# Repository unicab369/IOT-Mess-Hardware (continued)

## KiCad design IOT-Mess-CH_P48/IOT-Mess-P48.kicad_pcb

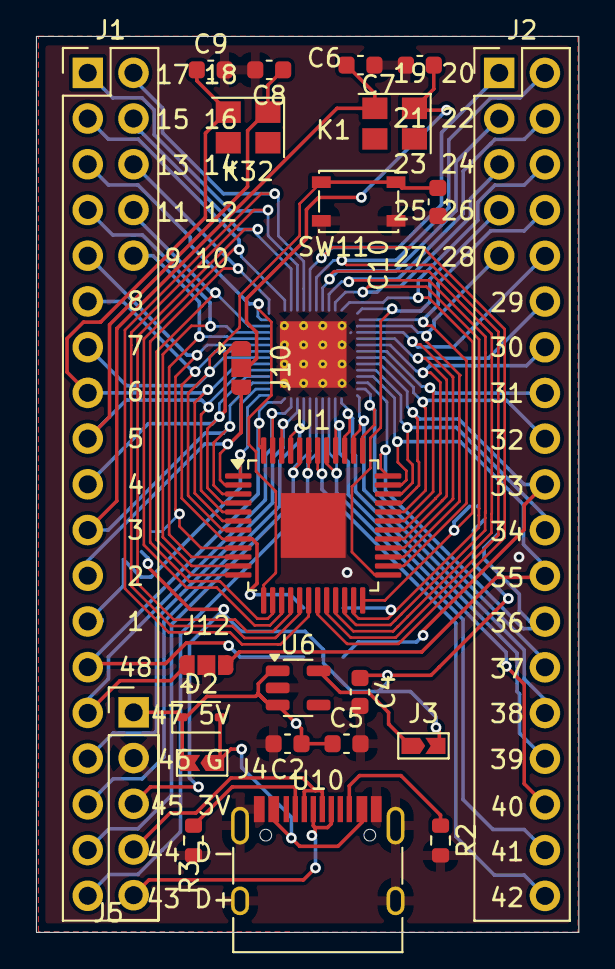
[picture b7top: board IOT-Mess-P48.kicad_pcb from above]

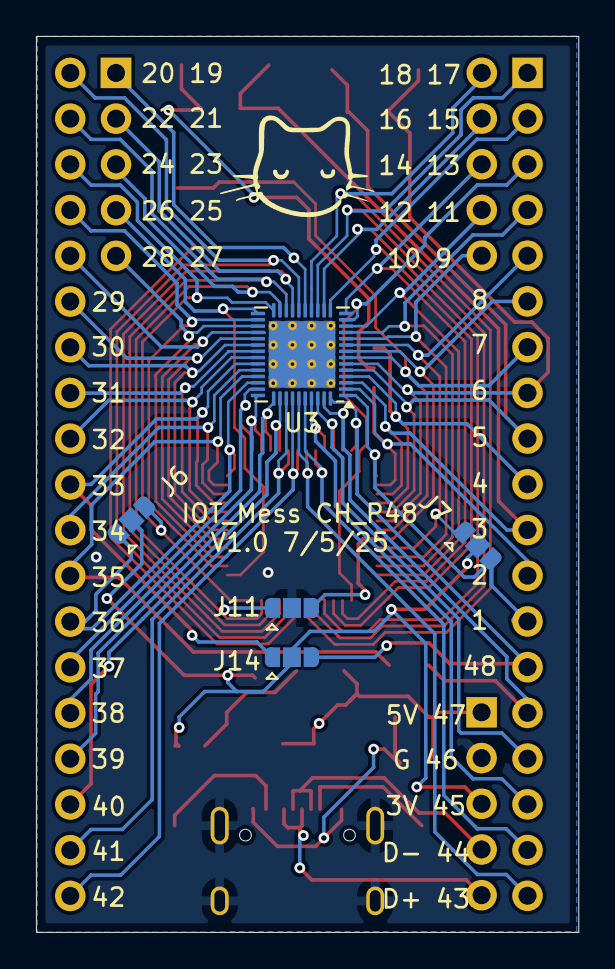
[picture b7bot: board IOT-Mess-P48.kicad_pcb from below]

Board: 2 copper layers, 30.1 x 49.8 mm, 29 parts (5 on the bottom side), 58 nets.

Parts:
C2: 10u; C_0603_1608Metric
C4, C5: 1u; C_0603_1608Metric
C6, C7: 12-25pF; C_0603_1608Metric
C8, C9: 15-30pF; C_0603_1608Metric
C10: .1u; C_0603_1608Metric
D2: 1N5819WS; D_SOD-323
J1, J2: Conn_02x19_Odd_Even; PinHeader_2x19_P2.54mm_Vertical
J3, J4: Jumper_2; Jumpper-triangle
J5: Conn_01x05_Pin; PinHeader_1x05_P2.54mm_Vertical
J6, J7, J10, J11, J12, J14: Jumper; Jumper-3_P1.3mm_Open_RoundedPad1.0x1.5mm
K1, K32: Crystal; Crystal_SMD_3225-4Pin_3.2x2.5mm
R2, R3: 5.1K; R_0603_1608Metric
SW11: SW_Push; SW_SPST_PTS810
U1: LQFP-48-1EP_7x7mm_P0.5mm_EP3.6x3.6mm
U3: CH32L103C8T6; QFN-48-1EP_5x5mm_P0.35mm_EP3.7x3.7mm_ThermalVias
U6: ME6211C33M5; SOT-23-5
U10: USB_C_Receptacle_USB2.0_16P; USB_C_Receptacle_HRO_TYPE-C-31-M-12

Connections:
5V: C2.1, C5.1, D2.1 (K), J4.2 (B), J5.1, U6.1 (V_{IN}), U6.3 (CE)
+3.3V: C4.1, J3.2 (B), J5.3, J6.2 (C), J7.2 (C), J14.2 (C)
D+: J5.5, U10.A6 (D+), U10.B6 (D+)
D-: J5.4, U10.A7 (D-), U10.B7 (D-)
GND: C2.2, C4.2, C5.2, C6.2, C7.2, C8.2, C9.2, C10.2, J5.2, J11.2 (C), J12.2 (C), R2.2, R3.2, SW11.2, U1.49 (VSS), U3.49 (VSS), U6.2 (V_{SS}), U10.A1 (GND), U10.A12 (GND), U10.B1 (GND), U10.B12 (GND), U10.S1 (SHIELD)
unnamed: D2.2 (A), J4.1 (A), U10.A4 (VBUS), U10.A9 (VBUS), U10.B4 (VBUS), U10.B9 (VBUS)
unnamed: J3.1 (A), U6.5 (V_{OUT})
unnamed: C7.1, J10.2 (C), K1.1
unnamed: R3.1, U10.A5 (CC1)
unnamed: R2.1, U10.B5 (CC2)
P_1: J1.25, J7.3 (B), U1.1 (VBAT), U3.1 (VBAT)
P_2: J1.23, J10.3 (B), U1.2 (PC13), U3.2 (PC13)
P_3: C6.1, J1.21, K1.2, U1.3 (PC14/OSC32_IN), U3.3 (PC14/OSC32_IN)
P_4: J1.19, J10.1 (A), U1.4 (PC15/OSC32_OUT), U3.4 (PC15/OSC32_OUT)
P_5: C8.1, J1.17, K32.1, U1.5 (PD0/OSC_IN), U3.5 (PD0/OSC_IN)
P_6: C9.1, J1.15, K32.2, U1.6 (PD1/OSC_OUT), U3.6 (PD1/OSC_OUT)
P_7: C10.1, J1.13, SW11.1, U1.7 (NRST), U3.7 (NRST)
P_8: J1.11, J11.3 (B), U1.8 (VSSA), U3.8 (VSSA)
P_9: J1.9, J7.1 (A), U1.9 (VDDA), U3.9 (VDDA)
P_10: J1.10, U1.10 (PA0/ADC0/WKUP), U3.10 (PA0/ADC0/WKUP)
P_11: J1.7, U1.11 (PA1/ADC1), U3.11 (PA1/ADC1)
P_12: J1.8, U1.12 (PA2/ADC2), U3.12 (PA2/ADC2)
P_13: J1.5, U1.13 (PA3/ADC3), U3.13 (PA3/ADC3)
P_14: J1.6, U1.14 (PA4/ADC), U3.14 (PA4/ADC4/ADC0)
P_15: J1.3, U1.15 (PA5/ADC5/SCK*), U3.15 (PA5/ADC5/ADC1/SCK*)
P_16: J1.4, U1.16 (PA6/ADC6/MISO*), U3.16 (PA6/ADC6/MISO*)
P_17: J1.1, U1.17 (PA7/ADC7/MOSI*), U3.17 (PA7/ADC7/MOSI*)
P_18: J1.2, U1.18 (PB0/ADC8), U3.18 (PB0/ADC8)
P_19: J2.1, U1.19 (PB1/ADC9), U3.19 (PB1/ADC9)
P_20: J2.2, U1.20 (PB2/BOTT), U3.20 (PB2/BOOT)
P_21: J2.3, U1.21 (PB10/SCL2*), U3.21 (PB10/SCL2*)
P_22: J2.4, U1.22 (PB11/SDA2*), U3.22 (BP11/SDA2*)
P_23: J2.5, J11.1 (A), U1.23 (VSS_1), U3.23 (VSS_1)
P_24: J2.6, J6.3 (B), U1.24 (VDD_VIO_1), U3.24 (VDD_1)
P_25: J2.7, U1.25 (PB12), U3.25 (PD12)
P_26: J2.8, U1.26 (PB13/SCK2*), U3.26 (PD13/SCK_2*)
P_27: J2.9, U1.27 (PB14/MISO2*), U3.27 (PD14/MISO_2*)
P_28: J2.10, U1.28 (PB15/MOSI2*), U3.28 (PD15/MOSI_2*)
P_29: J2.12, U1.29 (PA8), U3.29 (PA8)
P_30: J2.14, U1.30 (PA9), U3.30 (PA9)
P_31: J2.16, U1.31 (PA10), U3.31 (PA10)
P_32: J2.18, U1.32 (PA11/USB1_DM), U3.32 (PA11/USB_HDM)
P_33: J2.20, J14.1 (A), U1.33 (PA12/USB1_DP), U3.33 (PA12/USB_HDP)
P_34: J2.22, U1.34 (AP13/SWDIO), U3.34 (PA23/SWDIO)
P_35: J2.24, J12.3 (B), U1.35 (VSS_2), U3.35 (VSS_2)
P_36: J2.26, J6.1 (A), U1.36 (VDD_2), U3.36 (VDD_2)
P_37: J2.28, U1.37 (PA14/SWCLK), U3.37 (PA14/SWCLK)
P_38: J2.30, U1.38 (PA15), U3.38 (PA15)
P_39: J2.32, U1.39 (PB3), U3.39 (PB3)
P_40: J2.34, U1.40 (PB4), U3.40 (PB4)
P_41: J2.36, U1.41 (PB5), U3.41 (PB5)
P_42: J2.38, U1.42 (PB6/USB2_DM/SCL*), U3.42 (PB6/USB2_DM/SCL*)
P_43: J1.37, U1.43 (PB7/USB2_DP/SDA*), U3.43 (PB7/USB2_DP/SDA*)
P_44: J1.35, U1.44 (BOOT0), U3.44 (BOOT0)
P_45: J1.33, U1.45 (PB8), U3.45 (PB8)
P_46: J1.31, U1.46 (PB9), U3.46 (PB9)
P_47: J1.29, J12.1 (A), U1.47 (VSS_3), U3.47 (VSS_3)
P_48: J1.27, J14.3 (B), U1.48 (VDD_VIO_3), U3.48 (VDD_3)

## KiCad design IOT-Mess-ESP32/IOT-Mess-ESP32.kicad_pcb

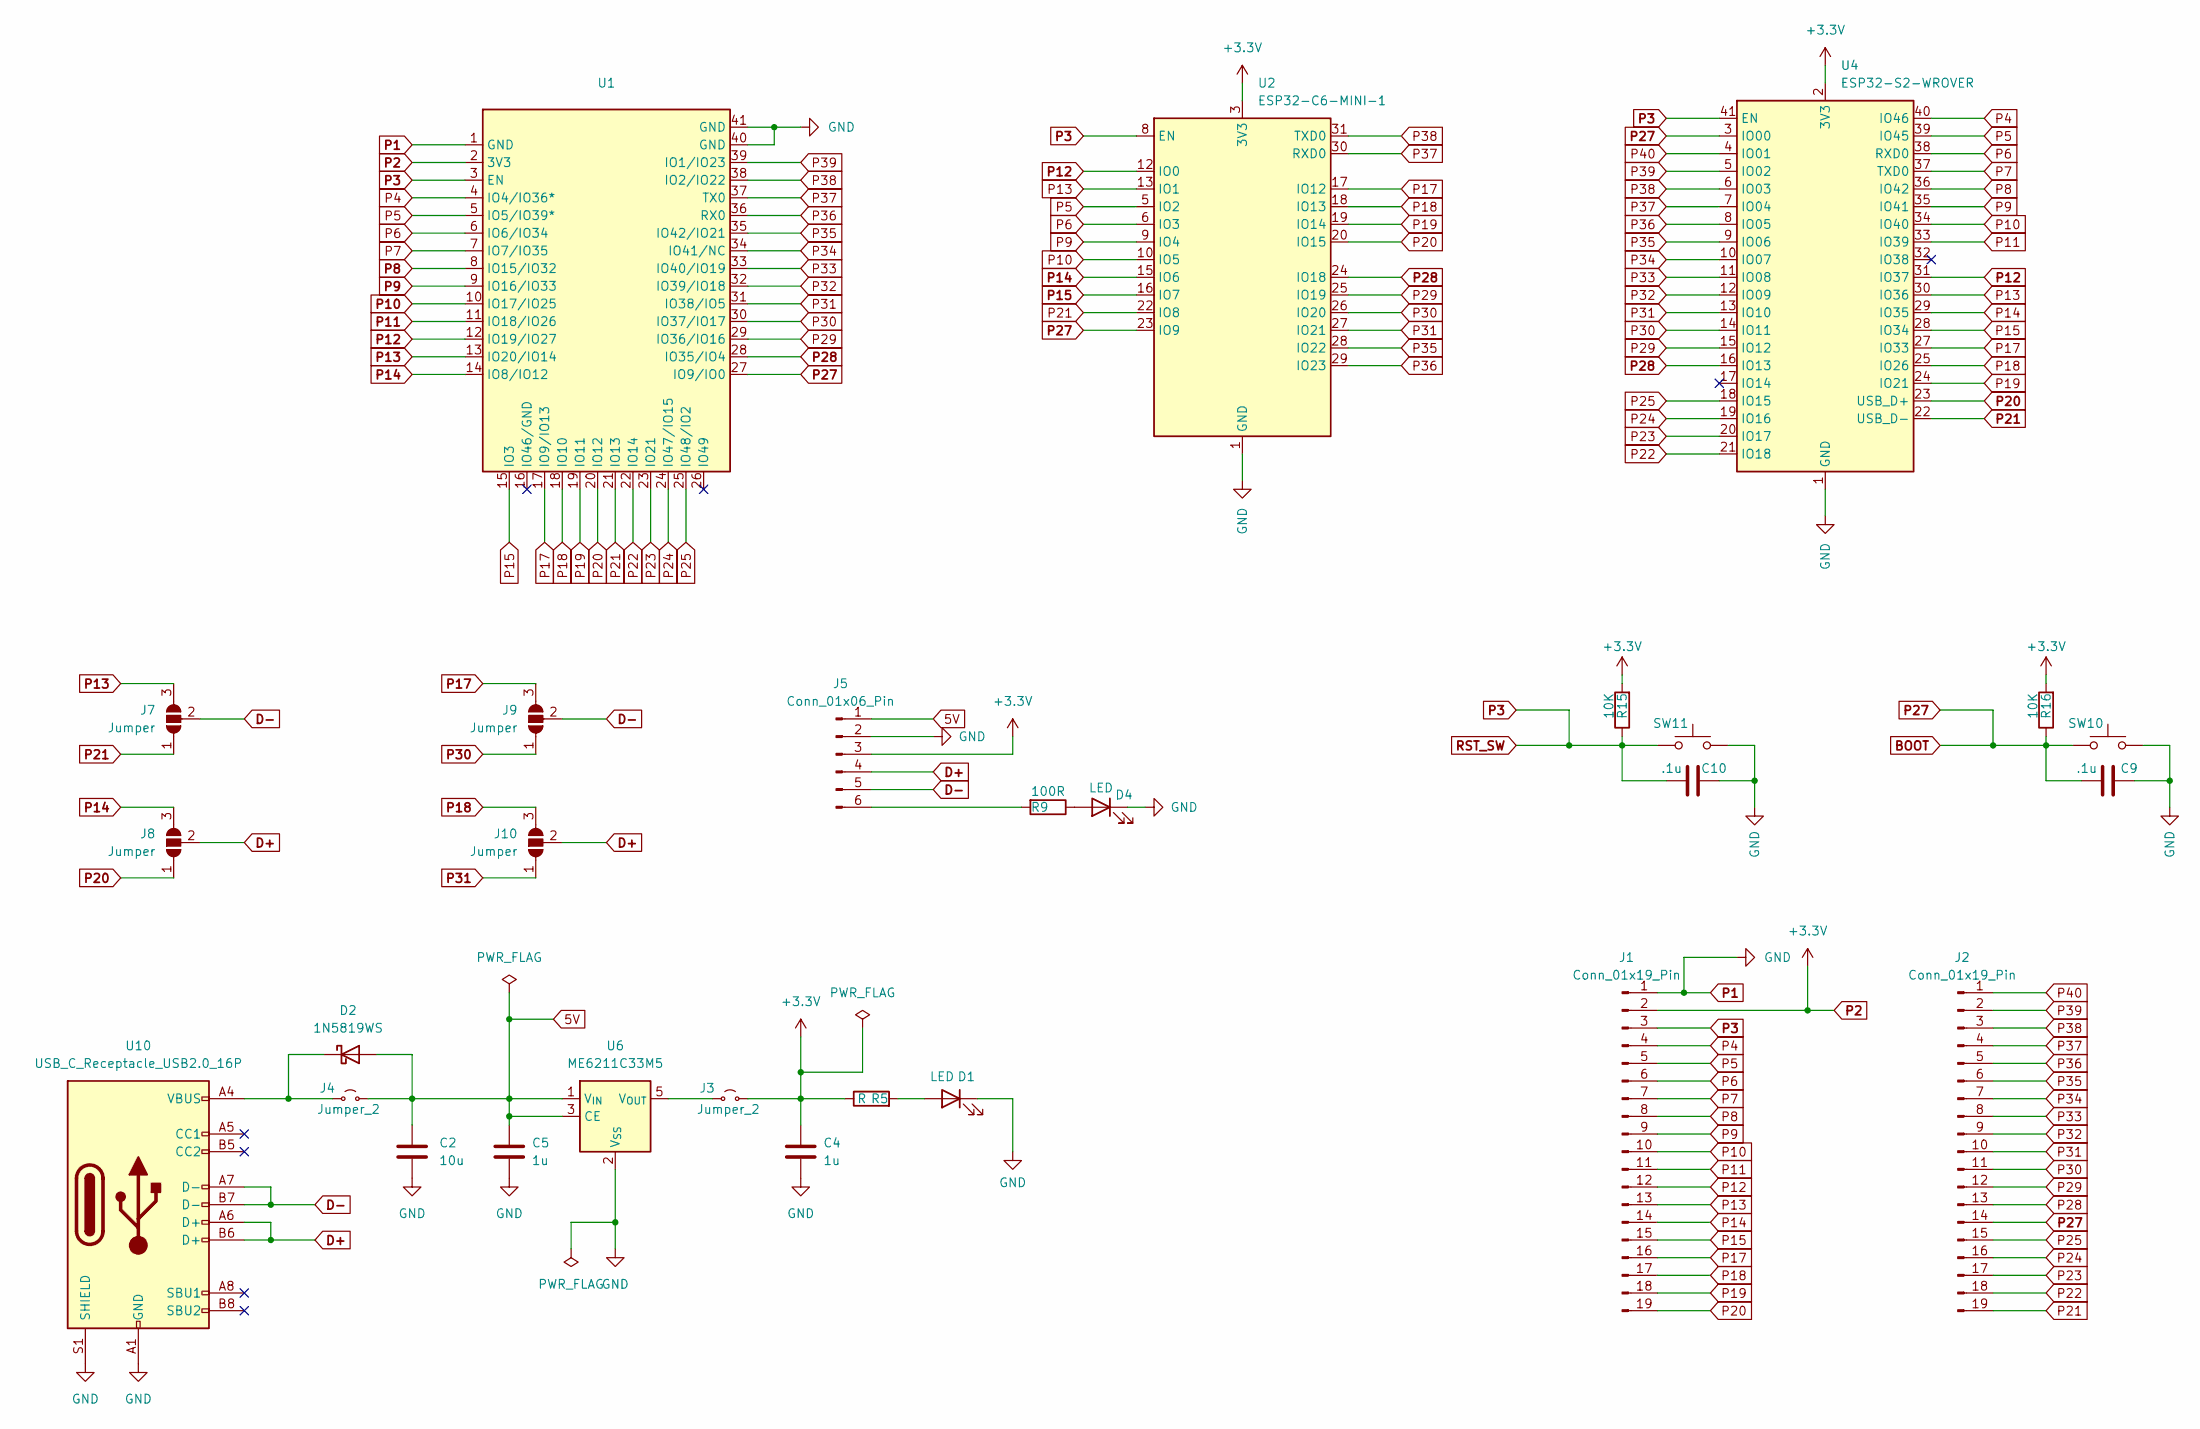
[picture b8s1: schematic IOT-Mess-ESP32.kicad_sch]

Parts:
C2: 10u; C_0603_1608Metric
C4, C5: 1u; C_0603_1608Metric
C9, C10: .1u; C_0603_1608Metric
D1, D4: LED; LED_0603_1608Metric
D2: 1N5819WS; D_SOD-323
J1, J2: Conn_01x19_Pin; PinHeader_1x19_P2.54mm_Vertical
J3, J4: Jumper_2; Jumpper-triangle
J5: Conn_01x06_Pin; PinHeader_1x06_P2.54mm_Vertical
J7, J8, J9, J10: Jumper; Jumper-3_P1.3mm_Open_RoundedPad1.0x1.5mm
R5: R; R_0603_1608Metric
R9: 100R; R_0603_1608Metric
R15, R16: 10K; R_0603_1608Metric
SW10, SW11: SW_Push; SW_SPST_PTS810
U1: ESP32-S3-WROOM-1
U2: ESP32-C6-MINI-1
U4: ESP32-S2-WROVER
U6: ME6211C33M5; SOT-23-5
U10: USB_C_Receptacle_USB2.0_16P; USB_C_Receptacle_HRO_TYPE-C-31-M-12

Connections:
5V: C2.1, C5.1, D2.2 (A), J4.2 (B), J5.1, U6.1 (V_{IN}), U6.3 (CE)
BOOT: C9.1, J2.14, R16.1, SW10.1, U1.27 (IO9/IO0), U2.23 (IO9), U4.3 (IO00)
D+: J5.4, J8.2 (C), J10.2 (C), U10.A6 (D+), U10.B6 (D+)
D-: J5.5, J7.2 (C), J9.2 (C), U10.A7 (D-), U10.B7 (D-)
unnamed: D1.2 (A), R5.2
unnamed: D2.1 (K), J4.1 (A), U10.A4 (VBUS), U10.A9 (VBUS), U10.B4 (VBUS), U10.B9 (VBUS)
unnamed: D4.2 (A), R9.1
unnamed: J3.1 (A), U6.5 (V_{OUT})
unnamed: J5.6, R9.2
P1: C2.2, C4.2, C5.2, C9.2, C10.2, D1.1 (K), D4.1 (K), J1.1, J5.2, SW10.2, SW11.2, U1.1 (GND), U1.40 (GND), U1.41 (GND), U2.1 (GND), U2.2 (GND), U2.11 (GND), U2.14 (GND), U2.36 (GND), U2.37 (GND), U2.38 (GND), U2.39 (GND), U2.40 (GND), U2.41 (GND), U2.42 (GND), U2.43 (GND), U2.44 (GND), U2.45 (GND), U2.46 (GND), U2.47 (GND), U2.48 (GND), U2.49 (GND), U2.50 (GND), U2.51 (GND), U2.52 (GND), U2.53 (GND), U4.1 (GND), U4.26 (GND), U4.42 (GND), U4.43 (GND), U6.2 (V_{SS}), U10.A1 (GND), U10.A12 (GND), U10.B1 (GND), U10.B12 (GND), U10.S1 (SHIELD)
P2: C4.1, J1.2, J3.2 (B), J5.3, R5.1, R15.2, R16.2, U1.2 (3V3), U2.3 (3V3), U4.2 (3V3)
P3: C10.1, J1.3, R15.1, SW11.1, U1.3 (EN), U2.8 (EN), U4.41 (EN)
P4: J1.4, U1.4 (IO4/IO36*), U4.40 (IO46)
P5: J1.5, U1.5 (IO5/IO39*), U2.5 (IO2), U4.39 (IO45)
P6: J1.6, U1.6 (IO6/IO34), U2.6 (IO3), U4.38 (RXD0)
P7: J1.7, U1.7 (IO7/IO35), U4.37 (TXD0)
P8: J1.8, U1.8 (IO15/IO32), U4.36 (IO42)
P9: J1.9, U1.9 (IO16/IO33), U2.9 (IO4), U4.35 (IO41)
P10: J1.10, U1.10 (IO17/IO25), U2.10 (IO5), U4.34 (IO40)
P11: J1.11, U1.11 (IO18/IO26), U4.33 (IO39)
P12: J1.12, U1.12 (IO19/IO27), U2.12 (IO0), U4.31 (IO37)
P13: J1.13, J7.3 (B), U1.13 (IO20/IO14), U2.13 (IO1), U4.30 (IO36)
P14: J1.14, J8.3 (B), U1.14 (IO8/IO12), U2.15 (IO6), U4.29 (IO35)
P15: J1.15, U1.15 (IO3), U2.16 (IO7), U4.28 (IO34)
P17: J1.16, J9.3 (B), U1.17 (IO9/IO13), U2.17 (IO12), U4.27 (IO33)
P18: J1.17, J10.3 (B), U1.18 (IO10), U2.18 (IO13), U4.25 (IO26)
P19: J1.18, U1.19 (IO11), U2.19 (IO14), U4.24 (IO21)
P20: J1.19, J8.1 (A), U1.20 (IO12), U2.20 (IO15), U4.23 (USB_D+)
P21: J2.19, J7.1 (A), U1.21 (IO13), U2.22 (IO8), U4.22 (USB_D-)
P22: J2.18, U1.22 (IO14), U4.21 (IO18)
P23: J2.17, U1.23 (IO21), U4.20 (IO17)
P24: J2.16, U1.24 (IO47/IO15), U4.19 (IO16)
P25: J2.15, U1.25 (IO48/IO2), U4.18 (IO15)
P28: J2.13, U1.28 (IO35/IO4), U2.24 (IO18), U4.16 (IO13)
P29: J2.12, U1.29 (IO36/IO16), U2.25 (IO19), U4.15 (IO12)
P30: J2.11, J9.1 (A), U1.30 (IO37/IO17), U2.26 (IO20), U4.14 (IO11)
P31: J2.10, J10.1 (A), U1.31 (IO38/IO5), U2.27 (IO21), U4.13 (IO10)
P32: J2.9, U1.32 (IO39/IO18), U4.12 (IO09)
P33: J2.8, U1.33 (IO40/IO19), U4.11 (IO08)
P34: J2.7, U1.34 (IO41/NC), U4.10 (IO07)
P35: J2.6, U1.35 (IO42/IO21), U2.28 (IO22), U4.9 (IO06)
P36: J2.5, U1.36 (RX0), U2.29 (IO23), U4.8 (IO05)
P37: J2.4, U1.37 (TX0), U2.30 (RXD0), U4.7 (IO04)
P38: J2.3, U1.38 (IO2/IO22), U2.31 (TXD0), U4.6 (IO03)
P39: J2.2, U1.39 (IO1/IO23), U4.5 (IO02)
P40: J2.1, U4.4 (IO01)

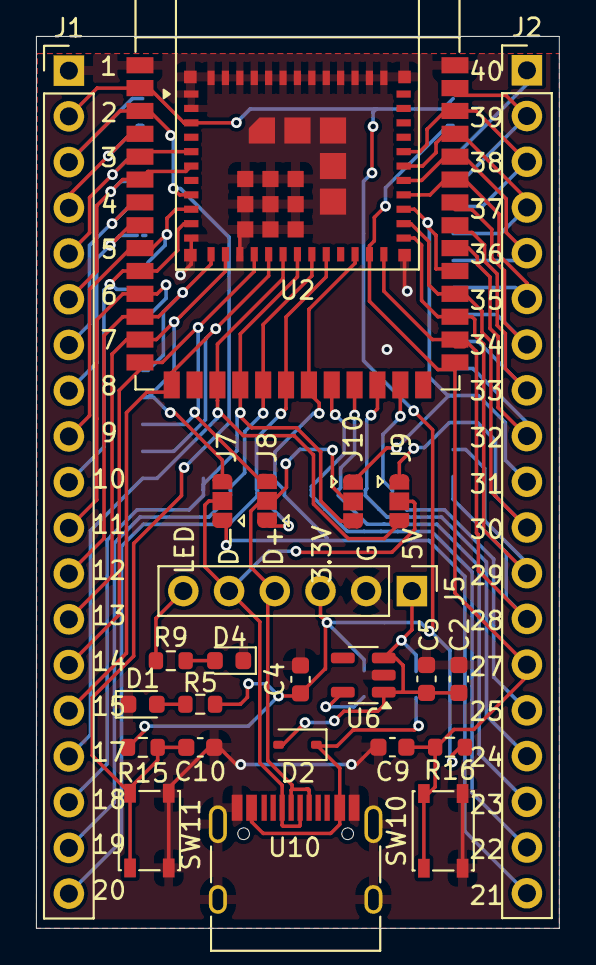
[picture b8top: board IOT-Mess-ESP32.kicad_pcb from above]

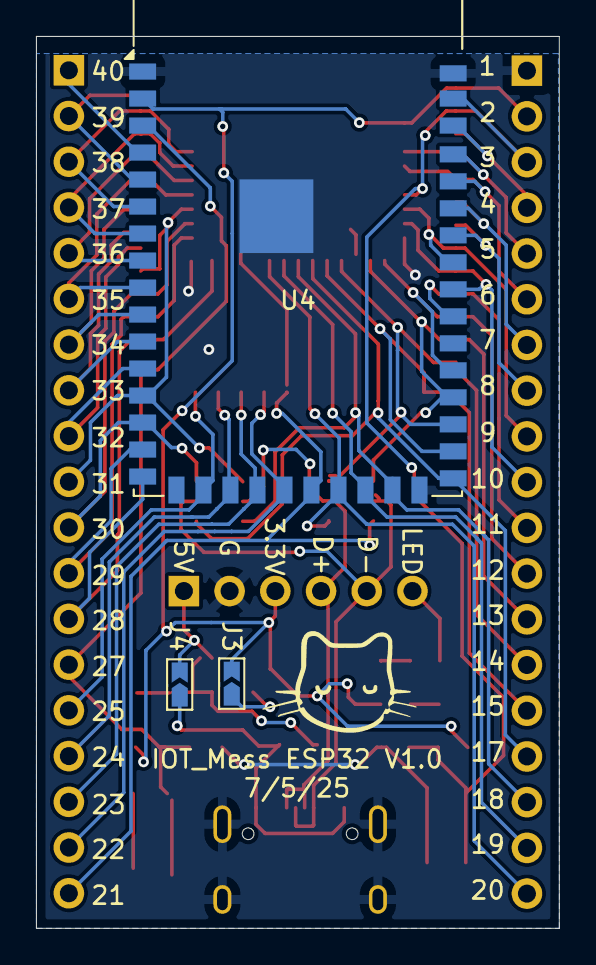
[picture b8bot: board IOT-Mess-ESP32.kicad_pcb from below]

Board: 2 copper layers, 29.0 x 49.5 mm, 28 parts (3 on the bottom side), 46 nets.
